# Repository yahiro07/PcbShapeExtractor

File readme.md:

# PCB Shape Extractor

Kicadの基板設計ファイルから外形やフットプリントの位置を抽出するツールです。

## サイト
https://miqsel.net/apps/pcb-shape-extractor

## デバッグ
```
yarn
yarn start
```

## ライセンス
MITライセンスです。

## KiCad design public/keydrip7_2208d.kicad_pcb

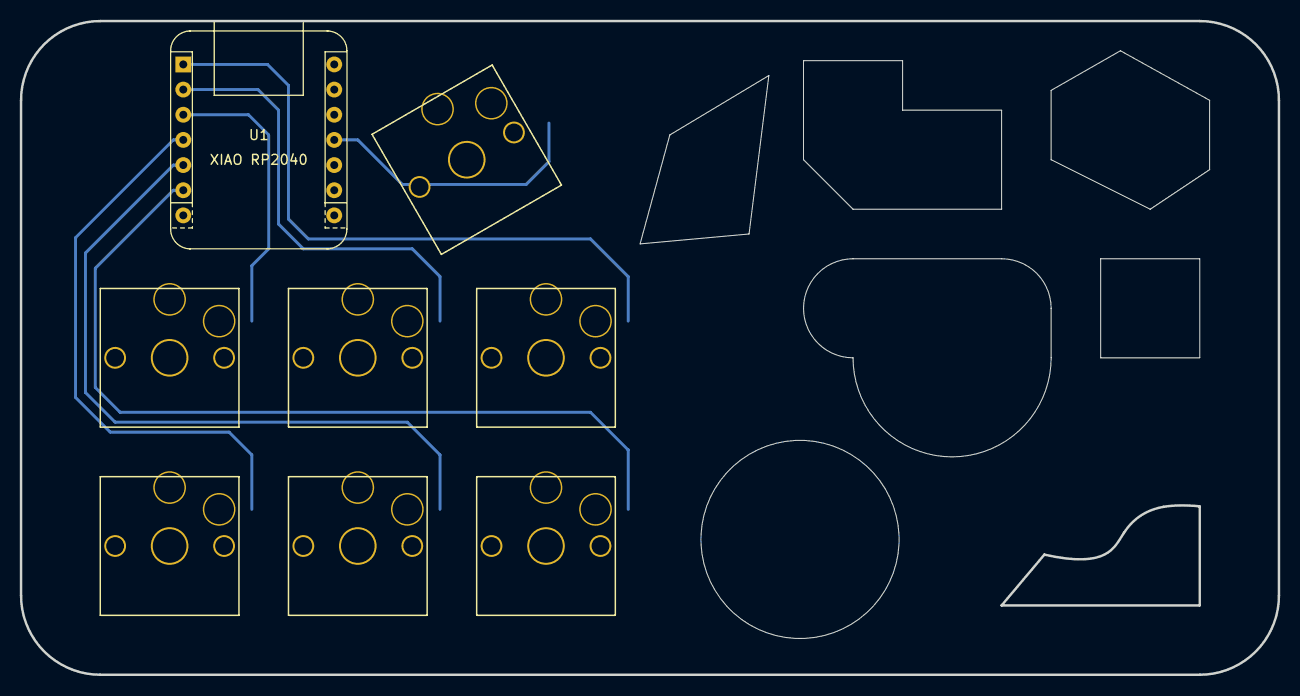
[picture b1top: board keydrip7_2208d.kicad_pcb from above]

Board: 2 copper layers, 127.0 x 66.0 mm, 8 parts (0 on the bottom side), 8 nets.

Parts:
KEY1, KEY2, KEY3, KEY4, KEY5, KEY6, KEY7: SW_KEY; choc_socket
U1: XIAO RP2040; xiao_rp2040

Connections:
GND: KEY1.2, KEY2.2, KEY3.2, KEY4.2, KEY5.2, KEY6.2, KEY7.2, U1.13 (GND)
key1: KEY1.1, U1.11 (GP3)
key2: KEY2.1, U1.3 (GP28)
key3: KEY3.1, U1.2 (GP27)
key4: KEY4.1, U1.1 (GP26)
key5: KEY5.1, U1.4 (GP29)
key6: KEY6.1, U1.5 (GP6)
key7: KEY7.1, U1.6 (GP7)

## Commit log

2022-09-10 初回コミット
2022-09-10 フォルダ階層を整理
2022-09-10 importの並び順を修正
2022-09-10 フットプリントのフィルタをビュー側に移動
2022-09-10 ファイルのロードを実装
2022-09-10 テストデータを表示
2022-09-10 抽出ワードの初期値を探索
2022-09-10 ファイル名を変更
2022-09-10 フォントを指定
2022-09-10 ストアに表示モードの状態管理を追加
2022-09-10 コンポーネントを追加
2022-09-10 グローバルスタイルを設定
2022-09-10 各セクションのUIを作成
2022-09-10 ページの表示を調整
2022-09-10 ボタンをコンポーネント化
2022-09-10 表示を調整
2022-09-10 フットプリントの表示を出し分け
2022-09-12 SVGの出力を実装
2022-09-12 JSONの書き出しを実装
2022-09-12 リファレンスを抽出
2022-09-12 リファレンスをプレビュー表示
2022-09-12 書き出し時に必須属性を付与
2022-09-12 バージョンを更新
2022-09-12 ogpタグを追加
2022-09-12 ヘッダにアイコンを追加
2022-09-12 faviconを追加
2022-09-12 不要なファイルを削除
2022-09-13 テストデータをボタンで読み込むように変更
2022-09-13 ヘッダコンポーネントを分離
2022-09-13 ドキュメントパネルを作成
2022-09-13 UIの操作可否を制御
2022-09-13 readmeを追加
2022-09-14 ファイル読み込み時の例外ハンドリングを追加
2022-09-14 文字列内での"のエスケープに対応
2022-09-14 boundingBoxの計算でキースイッチの大きさを考慮
2022-09-14 ドキュメントを更新
2022-09-14 trailing slashを付与
2022-09-14 OGPの画像を更新
